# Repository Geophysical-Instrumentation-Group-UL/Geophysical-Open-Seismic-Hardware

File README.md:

# Geophysical Open Seismic Hardware

The Geophysical Open Seismic Hardware initiative is brought to you by the Geophysical Instrumentation Group at Université Laval (GIGul) and is funded by the Fonds de Recherche du Québec- Nature et technologies (FRQNT). This open-hardware contribution provides Earth Scientists around the world with a reference design for multi-component borehole seismic array that can be deployed from a conventional wireline winch used in the mineral industry (1/8 single conductor armoured cable). This design is engineered around the Teensy 4.0 microcontroller board which is compatible with the Arduino ecosystem and will be familiar to engineers and tinkerers. Our design philosophy is to include easily sourced components as part of modules that can readily be modified for other geophysical acquisition projects.

This repository contains all the design files for the different printed circuit boards that are integrated in this modular design(PCB). The first module includes a 3 channel 24 bit ADC that can sample signals up to 32 kHz. The second module is a power supply module that is configured to condition the power used by downhole shuttle. We provide a KiCad version of these design files. In early 2022, we migrated the project from Altium to KiCad in order to meet the ethos of our project and allow more users to benefit from our developments. Here are images of the V2 prototype WorkerBoard as assembled in december 2022. 

 Details about specific aspects of the project can be found on in the doc repository. For more information and questions please contact arnaud.mercier05@gmail.com or christian.dupuis@ggl.ulaval.ca.

 The hardware development is under the TAPR Open Hardware License, while the firmware is under the GNU General Public License V3. License files are within respective directory.

Addition of November 2022 : 
A basic GUI is now available. This first version allows the user to configure and control the system with 3 shuttles. It also have a display window to anayse the individual shots as well as the stacked trace.

The article titled ``Geophysical Open Seismic Hardware: Design of a Vertical Seismic Profiling Instrument'' documents the performance and the first field validation of the prototype : https://openhardware.metajnl.com/articles/10.5334/joh.50

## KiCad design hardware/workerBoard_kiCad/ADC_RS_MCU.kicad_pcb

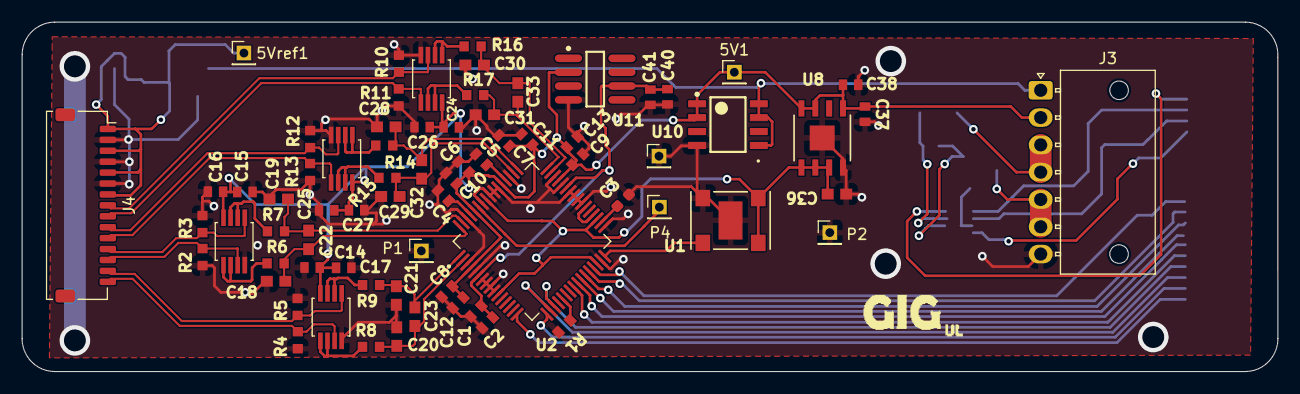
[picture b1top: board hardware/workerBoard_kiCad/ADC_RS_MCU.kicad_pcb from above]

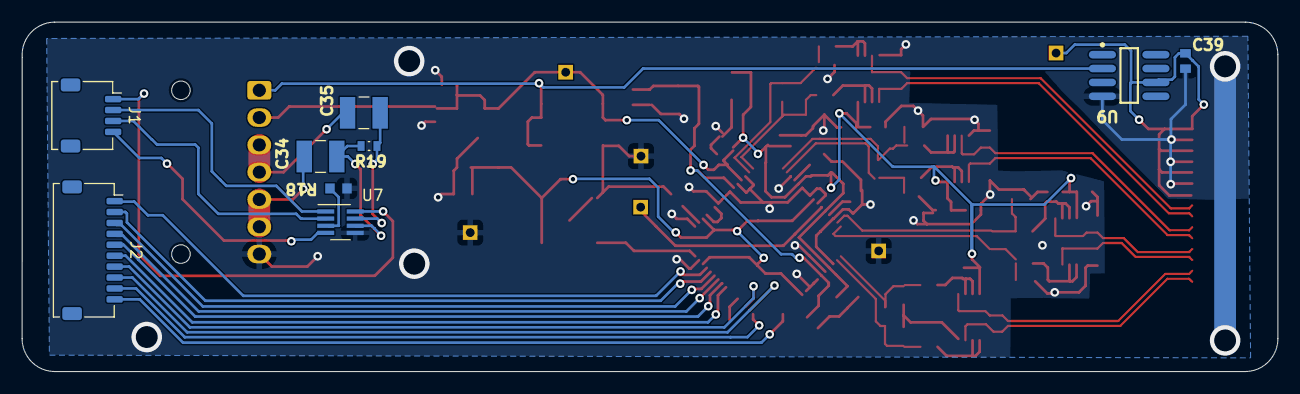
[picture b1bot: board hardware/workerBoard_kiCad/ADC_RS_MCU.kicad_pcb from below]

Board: 4 copper layers, 115.0 x 32.0 mm, 81 parts (9 on the bottom side), 56 nets.

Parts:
5V1, 5Vref1: Plug; PinHeader_1x01_P2.00mm_Vertical
C1, C4, C5, C6, C7, C8, C9, C16, C17, C26, C27, C37, C40: 1u; CAPC1608X90N
C2, C10, C11, C12, C13, C14, C15, C24, C25, C38, C39, C41: 0.1uF; CAPC1608X90N
C3: 10uF; CAPC1608X9N
C18, C19, C20, C21, C28, C29, C30, C31: 120pF; CAPC1608X90
C22, C23, C32, C33: 330pF; CAPC1608X90
C34, C35: 0.47uF-250V; CAPC3326X280N
C36: 2.2uF; CAPC1608X90
J1: Conn_01x04_Male; Molex_Pico-Clasp_202396-0407_1x04-1MP_P1.00mm_Horizontal
J2: Conn_01x10_Male; Molex_Pico-Clasp_202396-1007_1x10-1MP_P1.00mm_Horizontal
J3: Conn_01x07_Male; Molex_Nano-Fit_105313-xx07_1x07_P2.50mm_Horizontal
J4: Conn_01x15; Molex_Pico-Clasp_202396-1507_1x15-1MP_P1.00mm_Horizontal
P1, P2, P3, P4: Plug; PinHeader_1x01_P2.00mm_Vertical
R1: 100; RESC1508X55N
R2, R3, R4, R5, R10, R11, R12, R13: 1M; RESC1608X55N
R6, R7, R8, R9, R14, R15, R16, R17: 33; RESC1608X55N
R18: 1.5k; RESC1608X55N
R19: 120; RES_ERA3AEB121V
U1: DSC1001AI2-032.7680; DFN4_7X5_MCH
U2: AD7768-4BSTZ; QFP50P1200X1200X160-64N
U3, U4, U5, U6: RM_8_ADI; ADA4841-2YRMZ
U7: THVD8000DDFR; SOT-23-8_Handsoldering
U8: ADP7118ARDZ-3.3-R7; SOIC_08_EP_3P9X4P9_ADI
U9: ADR435BRZ; ADI-R-8_M
U10: REG103UA-5; D0008A_M
U11: ADR4540BRZ; ADI-R-8_M

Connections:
3.3MCU: J1.1, U7.8 (VCC)
5V: 5V1.1, C6.2, C7.2, C8.2, C9.2, C10.1, C11.1, C12.1, C13.1, C14.1, C15.1, C16.1, C17.1, C24.1, C25.1, C26.1, C27.1, C37.2, C38.1, J3.2, U2.4 (AVDD1A), U2.45 (AVDD1B), U2.53 (AVDD2B), U2.60 (AVDD2A), U3.8 (+VS), U4.8 (+VS), U5.8 (+VS), U6.8 (+VS), U8.5 (EN), U8.7 (VIN), U8.8 (VIN), U10.1 (VOUT), U10.2 (VOUT), U11.2 (VIN)
5V ref: 5Vref1.1, C39.1, J4.1, J4.3, J4.5, J4.7, U9.6 (VOUT)
12V: J3.1, U9.2 (VIN), U10.5 (EN), U10.7 (VIN), U10.8 (VIN)
A: C34.2, J3.5, J3.6
AIN0+: C18.2, C22.1, R6.2, U2.64 (AIN0+)
AIN0-: C19.1, C22.2, R7.2, U2.63 (AIN0-)
AIN1+: C20.2, C23.1, R8.2, U2.2 (AIN1+)
AIN1-: C21.1, C23.2, R9.2, U2.1 (AIN1-)
AIN2+: C28.2, C32.1, R14.2, U2.49 (AIN2+)
AIN2-: C29.1, C32.2, R15.2, U2.50 (AIN2-)
AIN3+: C30.2, C33.1, R16.2, U2.47 (AIN3+)
AIN3-: C31.1, C33.2, R17.2, U2.48 (AIN3-)
B: C35.2, J3.3, J3.4
CS: J2.10, U2.16 (ST0/!CS)
DCLK: J2.2, U2.28 (DCLK)
DOUT0: J2.3, U2.27 (DOUT0)
DOUT1: J2.4, U2.26 (DOUT1)
DOUT2: J2.5, U2.25 (DOUT2)
DOUT3: J2.6, U2.24 (DOUT3)
DRDY: J2.1, U2.29 (~DRDY\)
GND: C1.1, C2.2, C3.1, C4.1, C5.1, C6.1, C7.1, C8.1, C9.1, C10.2, C11.2, C12.2, C13.2, C14.2, C15.2, C16.2, C17.2, C18.1, C19.2, C20.1, C21.2, C24.2, C25.2, C26.2, C27.2, C28.1, C29.2, C30.1, C31.2, C36.2, C37.1, C38.2, C39.2, C40.1, C41.2, J3.7, J4.2, J4.4, J4.6, P1.1, P2.1, P3.1, R1.2, R2.1, R3.1, R4.1, R5.1, R10.1, R11.1, R12.2, R13.2, R18.1, U1.2 (GND), U1.5 (EPAD), U2.3 (AVSS1A), U2.5 (REF1-), U2.7 (AVSS), U2.8 (AVSS), U2.9 (AVSS), U2.10 (AVSS), U2.31 (XTAL1), U2.33 (DGND), U2.39 (AVSS), U2.40 (AVSS), U2.41 (AVSS), U2.42 (AVSS), U2.44 (REF2-), U2.46 (AVSS1B), U2.51 (AVSS2B), U2.54 (AVSS), U2.55 (DGND), U2.56 (FORMAT0), U2.58 (CLK_SEL), U2.62 (AVSS2A), U3.4 (-VS), U4.4 (-VS), U5.4 (-VS), U6.4 (-VS), U7.5 (GND), U8.4 (GND), U8.EPAD, U9.4 (GND), U10.4 (GND), U11.4 (GND)
IN0+: J4.13, R2.2, U3.3 (+IN1)
IN0-: J4.12, R3.2, U3.5 (+IN2)
IN1+: J4.15, R4.2, U4.3 (+IN1)
IN1-: J4.14, R5.2, U4.5 (+IN2)
IN2+: J4.10, R12.1, U6.3 (+IN1)
IN2-: J4.11, R13.1, U6.5 (+IN2)
IN3+: J4.8, R10.2, U5.3 (+IN1)
IN3-: J4.9, R11.2, U5.5 (+IN2)
MODE: J1.3, U7.2 (MODE)
unnamed: C3.2, U2.34 (DREGCAP)
unnamed: C4.2, U2.61 (REGCAPA)
unnamed: C5.2, U2.52 (REGCAPB)
unnamed: C34.1, R19.1, U7.6 (A)
unnamed: C35.1, R19.2, U7.7 (B)
unnamed: R1.1, U2.21 (DIN)
unnamed: R6.1, U3.1 (OUT1), U3.2 (-IN1)
unnamed: R7.1, U3.6 (-IN2), U3.7 (OUT2)
unnamed: R8.1, U4.1 (OUT1), U4.2 (-IN1)
unnamed: R9.1, U4.6 (-IN2), U4.7 (OUT2)
unnamed: R14.1, U6.1 (OUT1), U6.2 (-IN1)
unnamed: R15.1, U6.6 (-IN2), U6.7 (OUT2)
unnamed: R16.1, U5.1 (OUT1), U5.2 (-IN1)
unnamed: R17.1, U5.6 (-IN2), U5.7 (OUT2)
unnamed: R18.2, U7.3 (F_SET)
unnamed: U1.3 (OUT), U2.32 (XTAL2/MCLK)
RS485RX: J1.2, U7.1 (R)
RS485TX: J1.4, U7.4 (D)
SCLK: J2.9, U2.17 (SCLK)
SDI: J2.8, U2.18 (DEC1/SDI)
SDO: J2.7, U2.19 (DEC0/SDO)
SYNC: U2.36 (~SYNC_IN\), U2.38 (~SYNC_OUT\)
V3ref: C36.1, U1.1 (*STANDBY), U1.4 (VDD), U2.11 (FILTER/GPIO4), U2.30 (~RESET\), U2.35 (IOVDD), U2.57 (~PIN!/SPI\), U8.1 (VOUT), U8.2 (VOUT), U8.3 (SENSE/ADJ)
V4ref: C1.2, C2.1, C40.2, C41.1, U2.6 (REF1+), U2.43 (REF2+), U11.6 (VOUT)
VCM: P4.1, U2.59 (VCM)

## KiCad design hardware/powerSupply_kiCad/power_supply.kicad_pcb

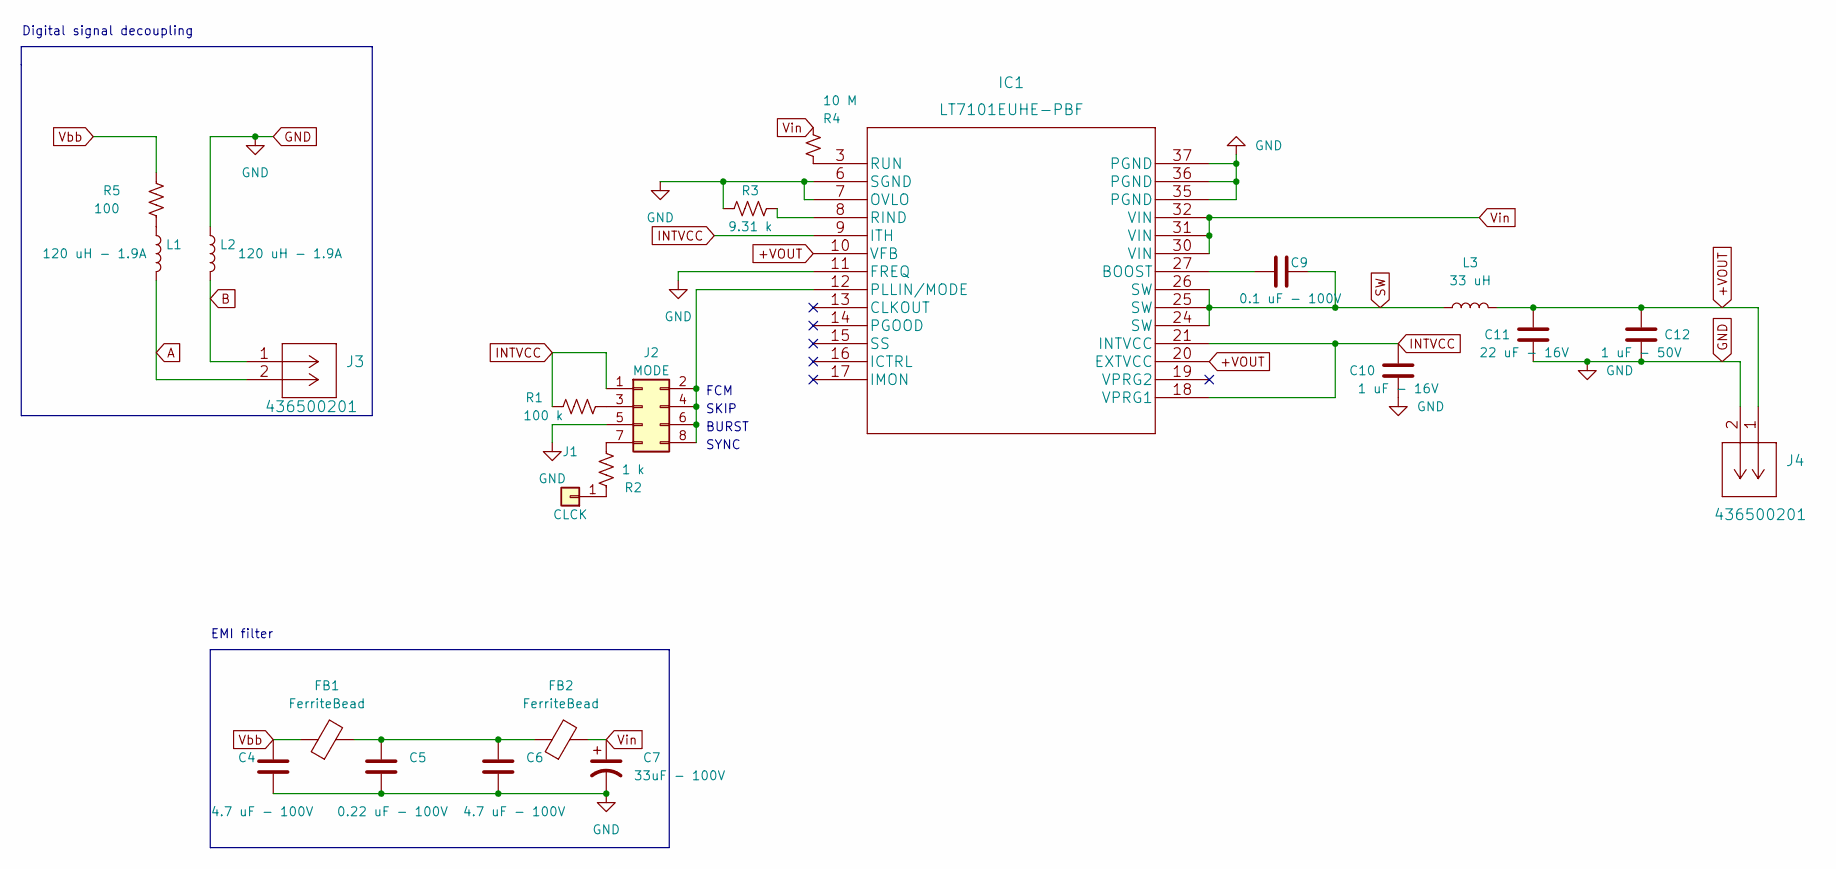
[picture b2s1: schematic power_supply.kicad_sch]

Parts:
C4, C6: 4.7 uF - 100V; C_1210_3225Metric
C5: 0.22 uF - 100V; C_0805_2012Metric
C7: 33uF - 100V; CP_Elec_10x10.5
C9: 0.1 uF - 100V; C_0805_2012Metric
C10: 1 uF - 16V; C_0805_2012Metric
C11: 22 uF - 16V; C_1210_3225Metric
C12: 1 uF - 50V; C_0805_2012Metric
FB1, FB2: FerriteBead; C_0805_2012Metric
IC1: LT7101EUHE-PBF
J1: CLCK; PinHeader_1x01_P2.54mm_Vertical
J2: MODE; PinHeader_2x04_P2.54mm_Vertical
J3, J4: 436500201
L1, L2: 120 uH - 1.9A; INDPM120120X805N
L3: 33 uH; SPM7054VT
R1: 100 k; R_0603_1608Metric
R2: 1 k; R_0603_1608Metric
R3: 9.31 k; R_0603_1608Metric
R4: 10 M; R_0805_2012Metric
R5: 100; TO-220-2_Vertical

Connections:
+VOUT: C11.1, C12.1, IC1.10 (VFB), IC1.20 (EXTVCC), J4.1, L3.2
A: J3.2, L1.2
B: J3.1, L2.2
GND: C4.2, C5.2, C6.2, C7.2, C10.2, C11.2, C12.2, IC1.6 (SGND), IC1.7 (OVLO), IC1.11 (FREQ), IC1.35 (PGND), IC1.36 (PGND), IC1.37 (PGND), J2.5, J4.2, L2.1, R3.1; also elsewhere on the board
INTVCC: C10.1, IC1.9 (ITH), IC1.18 (VPRG1), IC1.21 (INTVCC), J2.1, R1.1
unnamed: C5.1, C6.1, FB1.2, FB2.1
unnamed: C9.1, IC1.27 (BOOST)
unnamed: IC1.3 (RUN), R4.2
unnamed: IC1.8 (RIND), R3.2
unnamed: IC1.12 (PLLIN/MODE), J2.2, J2.4, J2.6, J2.8
unnamed: J1.1, R2.1
unnamed: J2.3, R1.2
unnamed: J2.7, R2.2
unnamed: L1.1, R5.2
SW: C9.2, IC1.24 (SW), IC1.25 (SW), IC1.26 (SW), L3.1
Vbb: C4.1, FB1.1, R5.1
Vin: C7.1, FB2.2, IC1.30 (VIN), IC1.31 (VIN), IC1.32 (VIN), R4.1

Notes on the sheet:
BURST
FCM
SKIP
EMI filter
SYNC
Digital signal decoupling

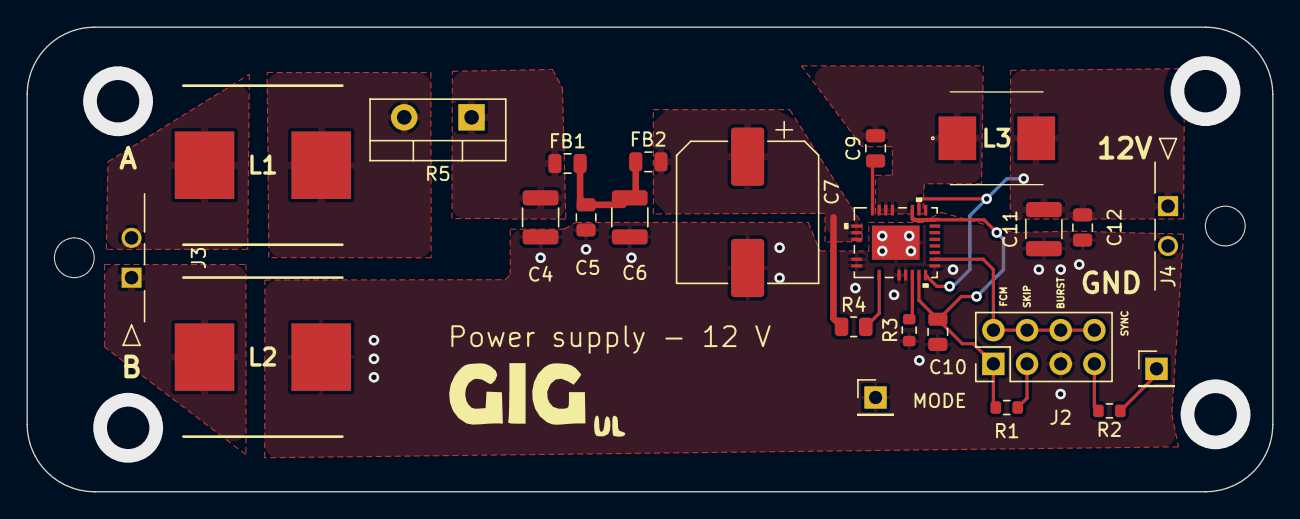
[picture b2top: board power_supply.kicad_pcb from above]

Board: 2 copper layers, 94.0 x 35.1 mm, 24 parts (0 on the bottom side), 17 nets.

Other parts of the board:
J5: GND; PinHeader_1x01_P2.54mm_Vertical

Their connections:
GND: J5.1; also elsewhere on the board

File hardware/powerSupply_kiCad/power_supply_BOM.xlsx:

Item | Quantity | Designator | Manufacturer_Name | Comment | Manufacturer Part Number | Mouser Part Number | Digikey Part Number | Description | Footprint
1 | 2 | C4, C6 | Taiyo Yuden Co., Ltd. | 4.7 uF - 100V | HMK325C7475KN-TE |  | 587-5038-1-ND | CAP CER 4.7UF 100V X7S 1210 | C_1210_3225Metric
2 | 1 | C5 | Taiyo Yuden Co., Ltd. | 0.22 uF - 100V | HMK212B7224KG-T |  | 587-2087-1-ND | CAP CER 0.22UF 100V X7R 0805 | C_0805_2012Metric
3 | 1 | C7 | Vishay | 33uF - 100V | 100SEV33M10X10.5 |  | 1189-3062-1-ND | CAP ALUM 33UF 20% 100V SMD | CP_Elec_10x10.5
4 | 1 | C9 | Murata | 0.1 uF - 100V | GRM21BR72A104KAC4L |  | 490-12005-1-ND | CAP CER 0.1UF 100V X7R 0805 | C_0805_2012Metric
5 | 1 | C10 | Kyocera AVX | 1 uF - 16V | 0805YC105KAT2A |  | 478-5034-1-ND | CAP CER 1UF 16V X7R 0805 | C_0805_2012Metric
6 | 1 | C11 | Murata | 22 uF - 16V | GRM32ER71C226KEA8L |  | 490-5890-1-ND | CAP CER 22UF 16V X7R 1210 | C_1210_3225Metric
7 | 1 | C12 | Samsung Electro-Mechanics | 1 uF - 50V | CL21B105KBFNNNG |  | 1276-6470-1-ND | CAP CER 1UF 50V X7R 0805 | C_0805_2012Metric
8 | 2 | FB1, FB2 | Würth Elecktronik | FerriteBead | 782853131 |  | 732-782853131CT-ND | WE-CBA SMT EMI SUPPRESSION FERRI | C_0805_2012Metric
9 | 1 | IC1 | Analog Devices Inc. | LT7101EUHE-PBF | LT7101EUHE#PBF |  | 505-LT7101EUHE#PBF-ND | Buck Switching Regulator IC Positive Adjustable 1V 1 Output 1A 36-WFQFN, 26 Lea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 | LT7101EUHE-PBF
10 | 1 | J1 |  | CLCK | 68000-201HLF |  | 609-68000-201HLF-ND | Through hole straight pin header, 1x01, 2.54mm pitch, single row | PinHeader_1x01_P2.54mm_Vertical
11 | 1 | J2 |  | MODE | 68000-201HLF |  | 609-68000-201HLF-ND | Through hole straight pin header, 2x04, 2.54mm pitch, double rows | PinHeader_2x04_P2.54mm_Vertical
12 | 2 | J3, J4 | Molex | 436500201 | 436500201 |  | WM1865-ND | CONN HEADER R/A 2POS 3MM | 436500201
13 | 1 | J5 |  | GND | 68000-201HLF |  | 609-68000-201HLF-ND | Through hole straight pin header, 1x01, 2.54mm pitch, single row | PinHeader_1x01_P2.54mm_Vertical
14 | 2 | L1, L2 | Coilcraft | 120 uH - 1.9A | MSS1278-124KLD | 994-MSS1278-124KLD |  | MSS1278-124KLD | INDPM120120X805N
15 | 1 | L3 | TDK | 33 uH | SPM7054VT-330M-D |  | 445-181516-1-ND | FIXED IND 33UH 3.4A 107.47 MOHM | SPM7054VT
16 | 1 | R1 | Vishay | 100 k | CRCW0603100KDHEAP |  | 541-100KAYCT-ND | RES SMD 100K OHM 0.5% 1/10W 0603 | R_0603_1608Metric
17 | 1 | R2 | Stackpole Electronics Inc | 1 k | RMCF0603FG1K00 |  | RMCF0603FG1K00CT-ND | RES 1K OHM 1% 1/10W 0603 | R_0603_1608Metric
18 | 1 | R3 | Stackpole Electronics Inc | 9.31 k | CRCW06039K31FKEA |  | 541-9.31KHCT-ND | RES SMD 9.31K OHM 1% 1/10W 0603 | R_0603_1608Metric
19 | 1 | R4 | Vishay | 10 M | RCS080510M0FKEA |  | 541-2854-1-ND | RES SMD 10M OHM 1% 0.4W 0805 | R_0805_2012Metric
20 | 1 | R5 | Ohmite | 100 | AP851 100R J |  | AP851100RJ-ND | RES 100 OHM 5% 50W TO220 | TO-220-2_Vertical

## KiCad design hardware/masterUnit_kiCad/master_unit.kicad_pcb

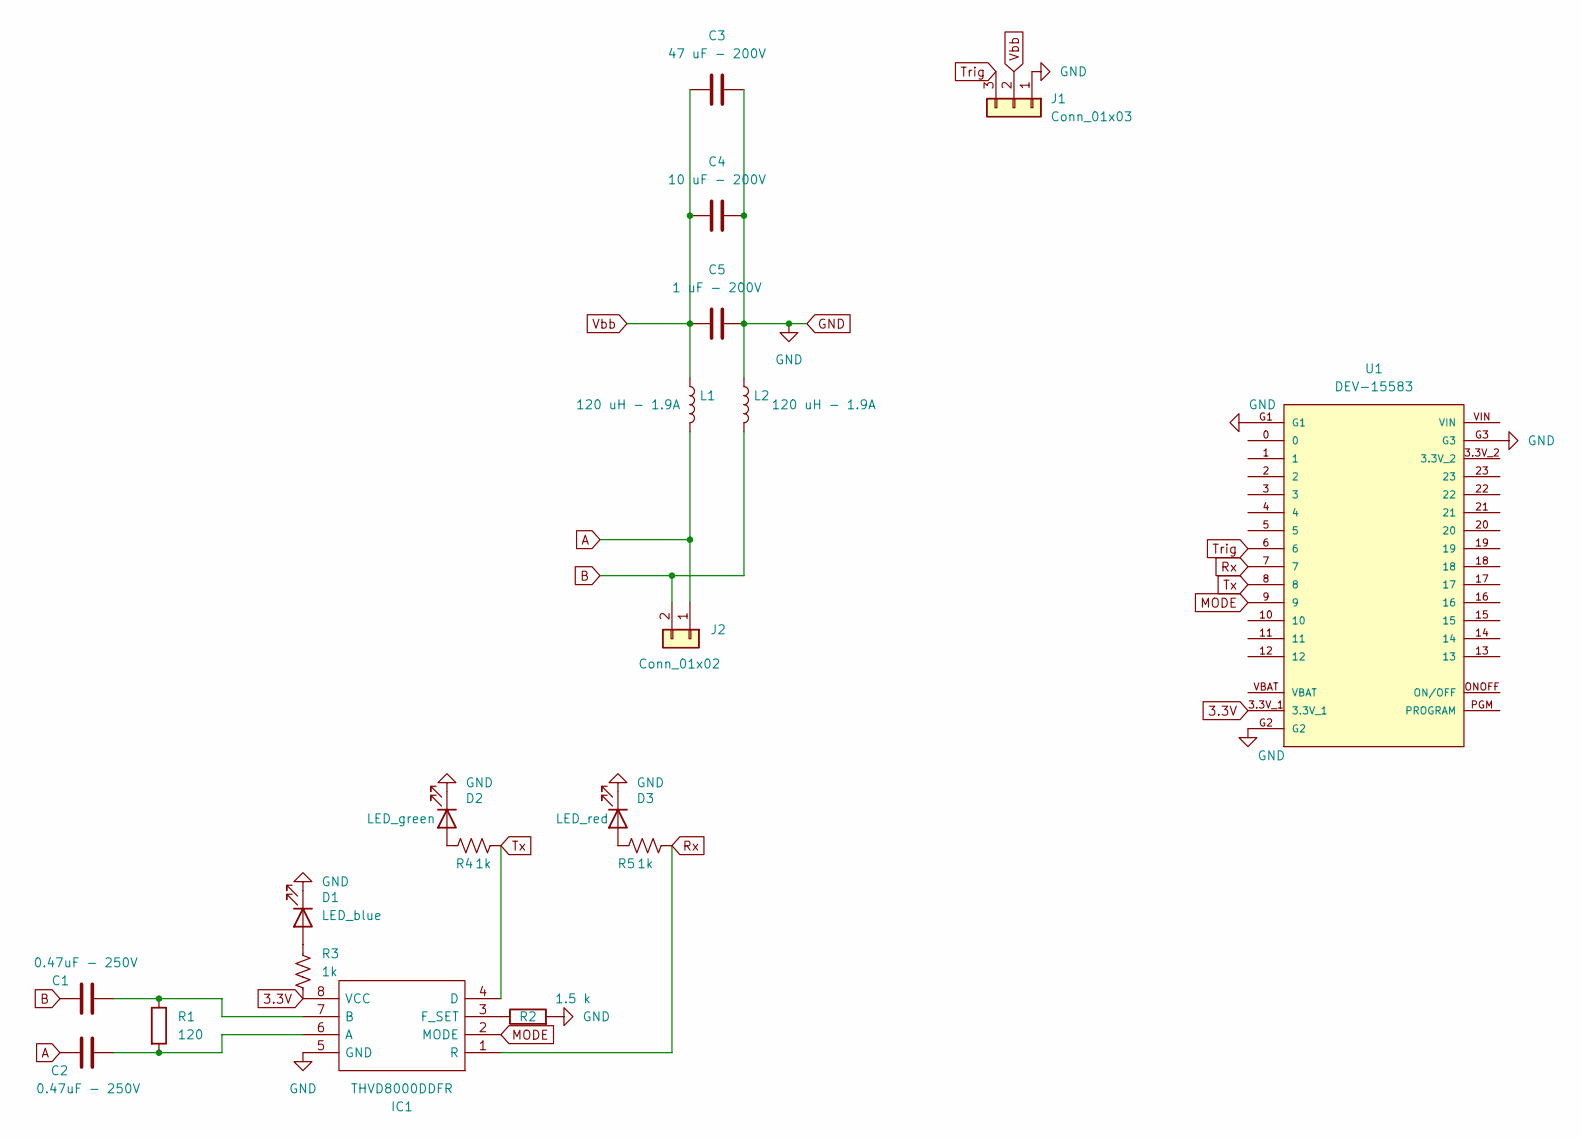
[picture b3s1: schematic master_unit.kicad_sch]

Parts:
C1, C2: 0.47uF - 250V; C_1210_3225Metric
C3: 47 uF - 200V; CP_Radial_D10.0mm_P5.00mm
C4: 10 uF - 200V; CP_Radial_D8.0mm_P3.50mm
C5: 1 uF - 200V; C_1812_4532Metric
D1: LED_blue; LED_1206_3216Metric
D2: LED_green; LED_1206_3216Metric
D3: LED_red; LED_1206_3216Metric
IC1: THVD8000DDFR; SOT65P280X110-8N; Mouser Part Number 595-THVD8000DDFR
J1: Conn_01x03; Banana_Jack_3Pin
J2: Conn_01x02; Banana_Jack_2Pin
L1, L2: 120 uH - 1.9A; INDPM120120X805N
R1: 120; R_0603_1608Metric
R2: 1.5 k; R_0603_1608Metric
R3, R4, R5: 1k; R_1206_3216Metric
U1: DEV-15583; teensy4.0

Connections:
3.3V: IC1.8 (VCC), R3.2, U1.3.3V_1
A: C2.1, J2.1, L1.2
B: C1.2, J2.2, L2.2
GND: C3.2, C4.2, C5.2, D1.1 (K), D2.1 (K), D3.1 (K), IC1.5 (GND), J1.1, L2.1, R2.2, U1.G1, U1.G2, U1.G3
MODE: IC1.2 (MODE), U1.9
unnamed: C1.1, IC1.7 (B), R1.1
unnamed: C2.2, IC1.6 (A), R1.2
unnamed: D1.2 (A), R3.1
unnamed: D2.2 (A), R4.1
unnamed: D3.2 (A), R5.1
unnamed: IC1.1 (R), R5.2, U1.7
unnamed: IC1.3 (F_SET), R2.1
unnamed: IC1.4 (D), R4.2, U1.8
Trig: J1.3, U1.6
Vbb: C3.1, C4.1, C5.1, J1.2, L1.1

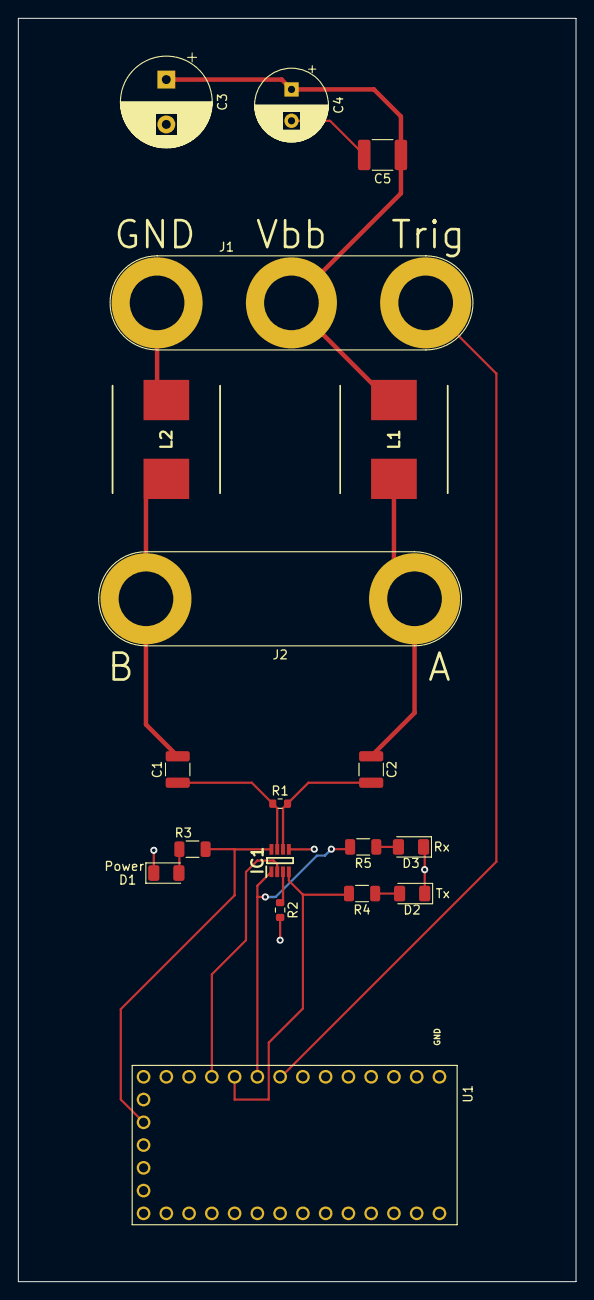
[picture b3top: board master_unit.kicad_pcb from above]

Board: 2 copper layers, 62.2 x 141.0 mm, 19 parts (0 on the bottom side), 15 nets.

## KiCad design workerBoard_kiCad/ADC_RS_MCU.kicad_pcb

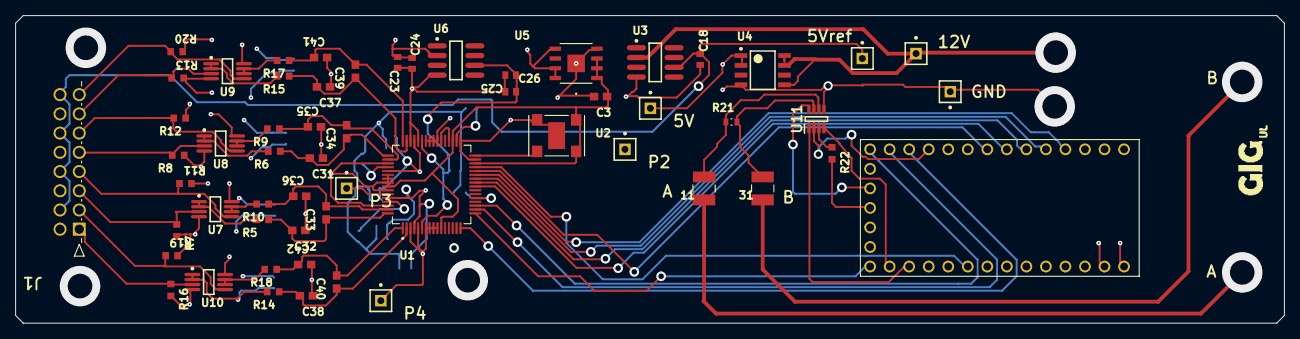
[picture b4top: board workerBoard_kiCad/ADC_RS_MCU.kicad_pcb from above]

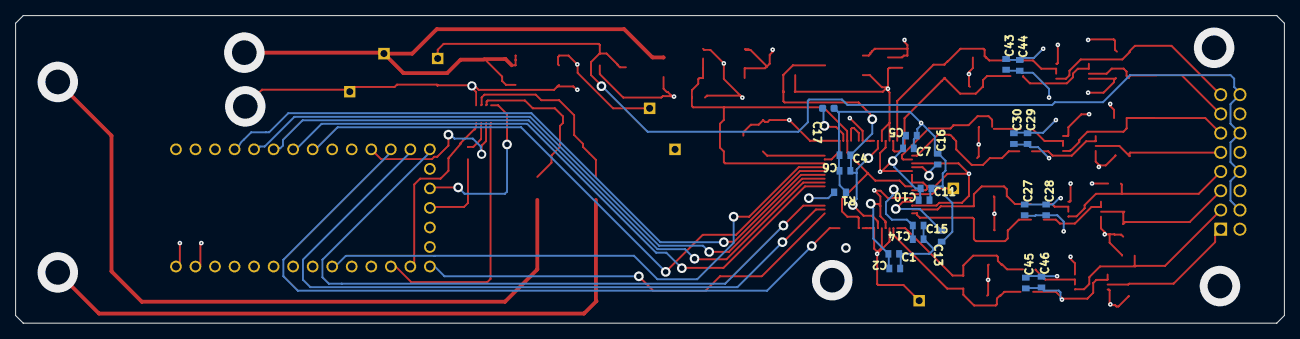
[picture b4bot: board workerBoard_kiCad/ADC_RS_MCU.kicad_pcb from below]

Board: 4 copper layers, 165.0 x 40.0 mm, 80 parts (22 on the bottom side), 55 nets.

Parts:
5V, 5Vref, 12V: Plug; PIN1
11, 31: 0.47uF-250V; CAPC3326X280N
C1, C6, C7, C11, C13, C15, C16, C23, C25, C28, C30, C44, C45: 1u; CAPC1608X90N
C2, C4, C5, C10, C14, C18, C24, C26, C27, C29, C43, C46: 0.1uF; CAPC1608X90N
C3: 2.2uF; CAPC1608X90
C17: 10uF; CAPC1608X9N
C31, C32, C35, C36, C37, C38, C41, C42: 120pF; CAPC1608X90
C33, C34, C39, C40: 330pF; CAPC1608X90
GND: Plug; PIN1
J1: 1053141216; CON_1053141216
P2, P3, P4: Plug; PIN1
R1: 100; RESC1508X55N
R5, R6, R9, R10, R14, R15, R17, R18: 33; RESC1608X55N
R7, R8, R11, R12, R13, R16, R19, R20: 1M; RESC1608X55N
R21: 120; RES_ERA3AEB121V
R22: 1.5k; RESC1608X55N
Teensy1: DEV-15583; MODULE_DEV-15583
U1: AD7768-4BSTZ; QFP50P1200X1200X160-64N
U2: DSC1001AI2-032.7680; DFN4_7X5_MCH
U3: ADR435BRZ; ADI-R-8_M
U4: REG103UA-5; D0008A_M
U5: ADP7118ARDZ-3.3-R7; SOIC_08_EP_3P9X4P9_ADI
U6: ADR4540BRZ; ADI-R-8_M
U7, U8, U9, U10: ADA4841-2YRMZ-RL; ADI-RM-8_M
U11: THVD8000DDFR; SOT65P280X110-8N

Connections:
3.3MCU: Teensy1.3.3V_1, U11.8 (VCC)
5V: 5V.1, C1.2, C2.1, C5.1, C7.2, C10.1, C11.2, C14.1, C15.2, C23.2, C24.1, C27.1, C28.1, C29.1, C30.1, C43.1, C44.1, Teensy1.VIN, U1.4 (AVDD1A), U1.45 (AVDD1B), U1.53 (AVDD2B), U1.60 (AVDD2A), U4.1 (VOUT), U4.2 (VOUT), U5.5 (EN), U5.7 (VIN), U5.8 (VIN), U6.2 (VIN)
5V ref: 5Vref.1, C18.1, J1.10, J1.12, J1.14, J1.16, U3.6 (VOUT)
12V: 12V.1, U3.2 (VIN), U4.5 (EN), U4.7 (VIN), U4.8 (VIN)
+5V: C45.1, C46.1
AIN0+: C32.2, C33.1, R5.2, U1.64 (AIN0+)
AIN0-: C33.2, C36.1, R10.2
AIN1+: C38.2, C40.1, R14.2, U1.2 (AIN1+)
AIN1-: C40.2, C42.1, R18.2, U1.1 (AIN1-)
AIN2+: C31.2, C34.1, R6.2, U1.49 (AIN2+)
AIN2-: C34.2, C35.1, R9.2, U1.50 (AIN2-)
AIN3+: C37.2, C39.1, R15.2, U1.47 (AIN3+)
AIN3-: C39.2, C41.1, R17.2, U1.48 (AIN3-)
CS: Teensy1.10, U1.16 (ST0/!CS)
DCLK: Teensy1.6, U1.28 (DCLK)
DOUT0: Teensy1.2, U1.27 (DOUT0)
DOUT1: Teensy1.3, U1.26 (DOUT1)
DOUT2: Teensy1.4, U1.25 (DOUT2)
DOUT3: Teensy1.5, U1.24 (DOUT3)
DRDY: Teensy1.18, U1.29 (~DRDY\)
GND: C1.1, C2.2, C3.2, C4.2, C5.2, C6.1, C7.1, C10.2, C11.1, C13.1, C14.2, C15.1, C16.1, C17.1, C18.2, C23.1, C24.2, C25.1, C26.2, C27.2, C28.2, C29.2, C30.2, C31.1, C32.1, C35.2, C36.2, C37.1, C38.1, C41.2, C42.2, C43.2, C44.2, C45.2, C46.2, GND.1, J1.9, J1.11, J1.13, J1.15, P2.1, P4.1, R1.2, R7.1, R8.2, R11.1, R12.2, R13.1, R16.1, R19.1, R20.1, R22.1, Teensy1.G3, U1.3 (AVSS1A), U1.5 (REF1-), U1.7 (AVSS), U1.8 (AVSS), U1.9 (AVSS), U1.10 (AVSS), U1.31 (XTAL1), U1.33 (DGND), U1.39 (AVSS), U1.40 (AVSS), U1.41 (AVSS), U1.42 (AVSS), U1.44 (REF2-), U1.46 (AVSS1B), U1.51 (AVSS2B), U1.54 (AVSS), U1.55 (DGND), U1.56 (FORMAT0), U1.58 (CLK_SEL), U1.62 (AVSS2A), U2.2 (GND), U2.5 (EPAD), U3.4 (GND), U4.4 (GND), U5.4 (GND), U5.EPAD, U6.4 (GND), U11.5 (GND)
IN0+: J1.3, R7.2, U7.3 (+IN_1)
IN0-: J1.4, R11.2, U7.5 (+IN_2)
IN1+: J1.1, R16.2, U10.3 (+IN_1)
IN1-: J1.2, R19.2, U10.5 (+IN_2)
IN2+: J1.5, R8.1, U8.3 (+IN_1)
IN2-: J1.6, R12.1, U8.5 (+IN_2)
IN3+: J1.7, R13.2, U9.3 (+IN_1)
IN3-: J1.8, R20.2, U9.5 (+IN_2)
MODE: Teensy1.9, U11.2 (MODE)
unnamed: 11.1, R21.1, U11.6 (A)
unnamed: 31.1, R21.2, U11.7 (B)
unnamed: C13.2, U1.61 (REGCAPA)
unnamed: C16.2, U1.52 (REGCAPB)
unnamed: C17.2, U1.34 (DREGCAP)
unnamed: R1.1, U1.21 (DIN)
unnamed: R5.1, U7.1 (OUT_1), U7.2 (-IN_1)
unnamed: R6.1, U8.1 (OUT_1), U8.2 (-IN_1)
unnamed: R9.1, U8.6 (-IN_2), U8.7 (OUT_2)
unnamed: R10.1, U7.6 (-IN_2), U7.7 (OUT_2)
unnamed: R14.1, U10.1 (OUT_1), U10.2 (-IN_1)
unnamed: R15.1, U9.1 (OUT_1), U9.2 (-IN_1)
unnamed: R17.1, U9.6 (-IN_2), U9.7 (OUT_2)
unnamed: R18.1, U10.6 (-IN_2), U10.7 (OUT_2)
unnamed: R22.2, U11.3 (F_SET)
unnamed: U1.32 (XTAL2/MCLK), U2.3 (OUT)
RS485RX: Teensy1.15, U11.1 (R)
RS485TX: Teensy1.14, U11.4 (D)
SCLK: Teensy1.13, U1.17 (SCLK)
SDI: Teensy1.11, U1.18 (DEC1/SDI)
SDO: Teensy1.12, U1.19 (DEC0/SDO)
SYNC: U1.36 (~SYNC_IN\), U1.38 (~SYNC_OUT\)
V3ref: C3.1, U1.11 (FILTER/GPIO4), U1.30 (~RESET\), U1.35 (IOVDD), U1.57 (~PIN!/SPI\), U2.1 (*STANDBY), U2.4 (VDD), U5.1 (VOUT), U5.2 (VOUT), U5.3 (SENSE/ADJ)
V4ref: C4.1, C6.2, C25.2, C26.1, U1.6 (REF1+), U1.43 (REF2+), U6.6 (VOUT)
VCM: P3.1, U1.59 (VCM)

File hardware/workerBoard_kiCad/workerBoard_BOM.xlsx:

Item | Quantity | Designator | Manufacturer_Name | Comment | Manufacturer Part Number | Mouser Part Number | Digikey Part Number | Description | Footprint
1 | 1 |  | PJRC | DEV-15583 | DEV-15583 |  | 1568-DEV-15583-ND | RT1062 Teensy 4.0 i.MX ARMÂ® CortexÂ®-M7 MPU Embedded Evaluation Board | MODULE_DEV-15583
2 | 2 | 1, 3 | KEMET | 0.47uF-250V | C1210X474KARACAUTO | 80-C1210X474KARAUTO |  | Multilayer Ceramic Capacitors MLCC - SMD/SMT 250V 0.47uF X7R 1210 10% AEC-Q200 | CAPC3326X280N
3 | 7 | 5V, 5Vref, 12V, GND, P2, P3, P4 | Amphenol ICC (FCI) | Plug | 68000-201HLF |  | 609-68000-201HLF-ND | CONN HEADER VERT 1POS | PIN1
4 | 13 | C1, C6, C7, C11, C13, C15, C16, C23, C25, C28, C30, C44, C45 | Kyocera AVX | 1u | 0603YC105MAT4A | 581-0603YC105MAT4A |  | Multilayer Ceramic Capacitors MLCC - SMD/SMT 16V 1uF X7R 0603 0.2 | CAPC1608X90N
5 | 12 | C2, C4, C5, C10, C14, C18, C24, C26, C27, C29, C43, C46 | Kyocera AVX | 0.1uF | 06033D104KAT2A | 581-06033D104K |  | Multilayer Ceramic Capacitors MLCC - SMD/SMT 25V 0.1uF X5R 0603 10% | CAPC1608X90N
6 | 1 | C3 | Kyocera AVX | 2.2uF | F981C225MMA |  | 478-8655-1-ND | CAP TANT 2.2UF 20% 16V 0603 | CAPC1608X90
7 | 1 | C17 | Murata | 10uF | GRT188R61A106ME13D | 81-GRT188R61A106ME3D |  | Multilayer Ceramic Capacitors MLCC - SMD/SMT X5R 10Vdc 10uF VDC&Temp Derate Rcmd | CAPC1608X9N
8 | 8 | C31, C32, C35, C36, C37, C38, C41, C42 | Kyocera AVX | 120pF | 06035A121GAT2A | 581-06035A121GAT2A |  | Multilayer Ceramic Capacitors MLCC - SMD/SMT 50V 120pF C0G 0603 2% | CAPC1608X90
9 | 4 | C33, C34, C39, C40 | Kyocera AVX | 330pF | 06033A331GAT2A | 581-06033A331G |  | Multilayer Ceramic Capacitors MLCC - SMD/SMT 25V 330pF C0G 0603 2% Tol | CAPC1608X90
10 | 1 | J1 | Molex Connector Corporation | 1053141216 | 1053141216 |  | WM15165-ND | CONN HEADER R/A 16POS 2.5MM | CON_1053141216
11 | 1 | R1 | Vishay Beyschlag/Draloric/BC Components | 100 | MCT0603MD1000DP500 |  | MCT0603-100-MDCT-ND | RES SMD 100 OHM 0.5% 0.15W 0603 | RESC1508X55N
12 | 8 | R5, R6, R9, R10, R14, R15, R17, R18 | YAGEO | 33 | RT0603BRD0733RL |  | 13-RT0603BRD0733RLCT-ND | RES SMD 33 OHM 0.1% 1/10W 0603 | RESC1608X55N
13 | 8 | R7, R8, R11, R12, R13, R16, R19, R20 | YAGEO | 1M | RT0603DRD071ML |  | 13-RT0603DRD071MLCT-ND | RES 1M OHM 0.5% 1/10W 0603 | RESC1608X55N
14 | 1 | R21 | Panasonic Electronic Components | 120 | ERA3AEB121V |  | P120DBCT-ND | RES SMD 120 OHM 0.1% 1/10W 0603 | RES_ERA3AEB121V
15 | 1 | R22 | YAGEO | 1.5k | RT0603BRD071K5L |  | YAG1570CT-ND | RES SMD 1.5K OHM 0.1% 1/10W 0603 | RESC1608X55N
16 | 1 | U1 | Analog Devices Inc | AD7768-4BSTZ | AD7768-4BSTZ-RL | 584-AD7768-4BSTZ-RL |  | 24 Bit Analog to Digital Converter 4 Input 4 Sigma-Delta 64-LQFP _10x10_ | QFP50P1200X1200X160-64N
17 | 1 | U2 | Microchip | DSC1001AI2-032.7680 | DSC1001AI2-032.7680 |  | DSC1001AI2-032.7680-ND | MEMS OSC XO 32.7680MHZ CMOS SMD | DFN4_7X5_MCH
18 | 1 | U3 | Analog Devices Inc | ADR435BRZ | ADR435BRZ-REEL7 |  | 505-ADR435BRZ-REEL7CT-ND | Ultralow Noise XFET Voltage Reference with Current Sink and Source Capability, 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 | ADI-R-8_M
19 | 1 | U4 | Texas Instruments | REG103UA-5 | REG103UA-5 |  | REG103UA-5-ND | Single Output Fast Transient Response LDO, 500 mA, Fixed 5 V Output, 2.1 to 15 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 | D0008A_M
20 | 1 | U5 | Analog Devices Inc | ADP7118ARDZ-3.3-R7 | ADP7118ARDZ-3.3-R7 |  | ADP7118ARDZ-3.3-R7CT-ND | IC REG LINEAR 3.3V 200MA 8SOIC | SOIC_08_EP_3P9X4P9_ADI
21 | 1 | U6 | Analog Devices Inc | ADR4540BRZ | ADR4540BRZ |  | 505-ADR4540BRZ-ND | Ultralow Noise, High Accuracy Voltage Reference, 4.096 V Output, 3 to 15 V Supp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 | ADI-R-8_M
22 | 4 | U7, U8, U9, U10 | Analog Devices Inc | ADA4841-2YRMZ-RL | ADA4841-2YRMZ-RL |  | ADA4841-2YRMZ-RLTR-ND | Double Channel Low Wide Band Noise Operational Amplifier, 80 MHz BW, 13 V/us SR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 | ADI-RM-8_M
23 | 1 | U11 | Texas Instruments | THVD8000DDFR | THVD8000DDFR |  | 296-THVD8000DDFRCT-ND | RS-485 TRANSCEIVER WITH OOK MODU | DDF0008A-IPC_A
24 | 1 |  | Molex Connector Corporation | Connector assembly | 1053251008 |  | WM15193-ND | NANO-FIT TPA V0 BLK 8 CKT
25 | 1 |  | Molex Connector Corporation | Connector assembly | 1053081216 |  | WM15025-ND | CONN RCPT HSG 16POS 2.50MM
26 | 1 |  | Molex Connector Corporation | Cable | 0797582140 |  | 900-0797582140-ND | NANO FIT TIN PLATED 300MM 20AWG

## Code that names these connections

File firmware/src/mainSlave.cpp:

#include <Arduino.h>
#include <ad7768.h> 
#include <command.h>
#include <stdio.h>
#include <cmath>
#include <SPI.h>
#include <Vector.h>
#include <string>

#define RS485Serial Serial3

int Mode = 9; // high = send = D2 led off, low = listen = D2 led high
command receivedCommand; 
int ODR;
int numberOfByte = 32;
int duration;
int samplingRate;
bool mustSendStatus = false;
bool mustSendData = false;
bool readyToTrig = false;
int workerStatus = IDLE;
int workerID = 1;
int chipSelectPin = 10;
ad7768_chip _default = {
		/* Configuration */
		.chipSelectPin = chipSelectPin,
		.power_mode = AD7768_ECO,
		.mclk_div = AD7768_MCLK_DIV_32,
		.dclk_div = AD7768_DCLK_DIV_8,
		.dec_rate = AD7768_DEC_X1024,
		.filt_type = AD7768_FILTER_SINC,

	};
ad7768_chip _seismic = {
		/* Configuration */
		.chipSelectPin = chipSelectPin,
		.power_mode = AD7768_ECO,
		.mclk_div = AD7768_MCLK_DIV_32,
		.dclk_div = AD7768_DCLK_DIV_8,
		.dec_rate = AD7768_DEC_X32,
		.filt_type = AD7768_FILTER_SINC,

	};
ad7768_chip configType = _seismic;

// pin declaration
int dout0 = 2;
int dout1 = 3;
int dout2 = 4;
int clck = 6;
int drdy = 18;


// ISR functions
void read_ISR();
void drdy_ISR();

// binary_data-ready flags and counter
volatile bool data_packet_ready = false;
volatile int acquisition_initial_time;
volatile int data_packet_counter = 0; 


// trigger state
volatile bool init_trig_detected = false;
volatile bool triggered_state = false;

// clock count for each binary_data packet
volatile int clck_count = 0;

// binary_data buffer and precalculated 2s power
volatile int expo [32] = {0,0,0,0,0,0,0,0,pow(2,23),pow(2,22),pow(2,21),pow(2,20),
pow(2,19),pow(2,18),pow(2,17),pow(2,16),pow(2,15),pow(2,14),
pow(2,13),pow(2,12),pow(2,11),pow(2,10),pow(2,9),pow(2,8),pow(2,7),pow(2,6),pow(2,5),
pow(2,4),pow(2,3),pow(2,2),pow(2,1),pow(2,0)};
volatile int binary_data0[32];
volatile double integer_data0 = 0;

volatile int binary_data1[32];
volatile double integer_data1 = 0;

volatile int binary_data2[32];
volatile double integer_data2 = 0;




int number_of_data_packet =1600;

// vector that holds a complete acquisition
int storage_arrayD0[16000]; //TODO: This maximum array size is 0.5 sec for 32 khz ODR
int storage_arrayT0[16000];
Vector<int> data0(storage_arrayD0);
Vector<int> time(storage_arrayT0);

int storage_arrayD1[16000]; //TODO: This maximum array size is 0.5 sec for 32 khz ODR
// int storage_arrayT1[32000];
Vector<int> data1(storage_arrayD1);
// Vector<int> time0(storage_arrayT1);

int storage_arrayD2[16000]; //TODO: This maximum array size is 0.5 sec for 32 khz ODR
// int storage_arrayT2[32000];
Vector<int> data2(storage_arrayD2);
// Vector<int> time(storage_arrayT2);

// When the lenght of the array is 32k the memory is overflowing.

void setup() {

  RS485Serial.begin(115200);
  Serial.begin(115200);   
  pinMode(Mode,OUTPUT);
  digitalWrite(Mode,LOW);
  SPI.begin();
  pinMode(dout0, INPUT);
  pinMode(drdy, INPUT_PULLDOWN);
  pinMode(clck, INPUT);
  pinMode(chipSelectPin, OUTPUT);

  delay(100);
  ad7768_setup(configType);
}

void loop() {

if(RS485Serial.available () >0 and readyToTrig == false) 
{
  // String test;

  receivedCommand = readCommand(&RS485Serial);
  // Serial.println(receivedCommand.def);
  // Serial.println(receivedCommand.workerId);
  // test = RS485Serial.readStringUntil('\n');
  // Serial.println(test);
  if (receivedCommand.type == GLOBAL or receivedCommand.workerId == workerID)
  {
    // Serial.println("called");
    // Serial.println(receivedCommand.def);
    // Serial.println(receivedCommand.workerId);

  if (receivedCommand.def == ARM)
  {
    workerStatus = ARMED;
    Serial.println("armed");
    data_packet_counter = 0;
    readyToTrig = true;

    attachInterrupt(digitalPinToInterrupt(drdy), drdy_ISR, RISING);
    attachInterrupt(digitalPinToInterrupt(clck), read_ISR, FALLING);
  }
  else if (receivedCommand.def == STATUS)
  {
    digitalWrite(Mode,HIGH);
    delay(5);
    sendWorkerStatus(&RS485Serial,workerStatus,workerID);
    delay(5);
    digitalWrite(Mode,LOW);
    delay(5);
  }
  else if (receivedCommand.def == CONFIG)
   {
    //  Serial.print(receivedCommand.adcConfig);
     Serial.print("config");
     if (receivedCommand.adcConfig == DEFAULT)
     {configType = _default;}
     else if (receivedCommand.adcConfig == SEISMIC)
     {configType = _seismic;} 
     int index = receivedCommand.data.indexOf("T");   
     samplingRate = receivedCommand.data.substring(0,index).toInt();
     duration = receivedCommand.data.substring(index+1).toInt();
    if (samplingRate == 32)
     {
      configType.dec_rate = AD7768_DEC_X32;
      }
    else if (samplingRate == 16)
      {
      configType.dec_rate = AD7768_DEC_X64;
      }
    else if (samplingRate == 8)
      {
      configType.dec_rate = AD7768_DEC_X128;
      }
    else if (samplingRate == 4)
      {
      configType.dec_rate = AD7768_DEC_X256;
      }
    else if (samplingRate == 2)
      {
      configType.dec_rate = AD7768_DEC_X512;
      }
    else if (samplingRate == 1)
      {
      configType.dec_rate = AD7768_DEC_X1024;
      }

     ad7768_setup(configType);
     workerStatus = CONFIGURED;

    delay(5);
    digitalWrite(Mode,HIGH);
    delay(5);
    sendWorkerStatus(&RS485Serial,workerStatus,workerID);
    delay(5);
    digitalWrite(Mode,LOW);


    number_of_data_packet =  int(((duration/1000.0) * (samplingRate*1000.0)));
    delay(5);
    digitalWrite(Mode,HIGH);
    delay(5);



    // RS485Serial.println(number_of_data_packet);

    // RS485Serial.println(receivedCommand.data);
    // RS485Serial.println(receivedCommand.data.substring(index+1).toInt());
    // ODR = print_config(configType, &RS485Serial);
    // RS485Serial.flush();
    delay(5);
    RS485Serial.println('e');
        delay(5);

    RS485Serial.println('s');
    digitalWrite(Mode,LOW);

 
    // Serial.println(number_of_data_packet);
    workerStatus = IDLE;
    

   }
  else if (receivedCommand.def == HARVEST)
  {
    mustSendData = true;
    Serial.println("called for harvest");
  }
  }
}
   

  if (mustSendData == true)
  {
    digitalWrite(Mode,HIGH);
     delay(5);
    RS485Serial.print(workerID);RS485Serial.println('w');
    delay(5);
    RS485Serial.print(number_of_data_packet);RS485Serial.println(':');
    delay(5);
    for (int i = 0; i < number_of_data_packet; i++)
      {
        RS485Serial.print(time.at(i));RS485Serial.print(",");
        RS485Serial.print(data0.at(i));RS485Serial.print(",");
        RS485Serial.print(data1.at(i));RS485Serial.print(",");
        RS485Serial.print(data2.at(i));
        RS485Serial.print(':');
        delay(1);
      }
    RS485Serial.flush();
    digitalWrite(Mode,LOW);
    mustSendData = false;
    workerStatus = IDLE;
    time.clear();
    data0.clear();
    data1.clear();
    data2.clear();
  }


noInterrupts();
if (readyToTrig == true and triggered_state == false)
{
 if (RS485Serial.find('t'))
{
    acquisition_initial_time = micros();
    triggered_state = true;
  }
}
if (data_packet_ready == true and triggered_state == true)
{		

    data0.push_back(integer_data0);
    data1.push_back(integer_data1);
    data2.push_back(integer_data2);
    time.push_back(micros() - acquisition_initial_time);

		data_packet_ready = false;
		data_packet_counter += 1;

		if (data_packet_counter == number_of_data_packet)
		{
      workerStatus = DATAREADY;
      // mustSendStatus = true;
			triggered_state = false;
      readyToTrig = false;
      data_packet_counter = 0;
      detachInterrupt(digitalPinToInterrupt(drdy));
      detachInterrupt(digitalPinToInterrupt(clck));
		}

}
interrupts();
}

void read_ISR() {
if (clck_count < 32){ // because the output is 32 bit long
// delayNanoseconds(10);
binary_data0[clck_count] = digitalRead(dout0);
binary_data1[clck_count] = digitalReadFast(dout1);
binary_data2[clck_count] = digitalReadFast(dout2);
clck_count += 1;


}
else if (clck_count == 33){ // directly after the last bit
	data_packet_ready = true;
	for (int i = 8; i < 32; i++) { // data bit is from 8 to 32
      integer_data0 +=  expo[i] * binary_data0[i];
			integer_data1 +=  expo[i] * binary_data1[i];
      integer_data2 +=  expo[i] * binary_data2[i];

			}
	clck_count += 1;

}

else {
	clck_count += 1;
}
}

void drdy_ISR(){
	if (triggered_state == true)
	{
	clck_count = 0;
	integer_data0 = 0;	
  integer_data1 = 0;	
  integer_data2 = 0;	
	}
	

}

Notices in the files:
parts and their libraries:
Copyright 2021 Accelerated Designs. All rights reserved.
COPYRIGHT: Copyright (C) 2021 Ultra Librarian. All rights reserved.
